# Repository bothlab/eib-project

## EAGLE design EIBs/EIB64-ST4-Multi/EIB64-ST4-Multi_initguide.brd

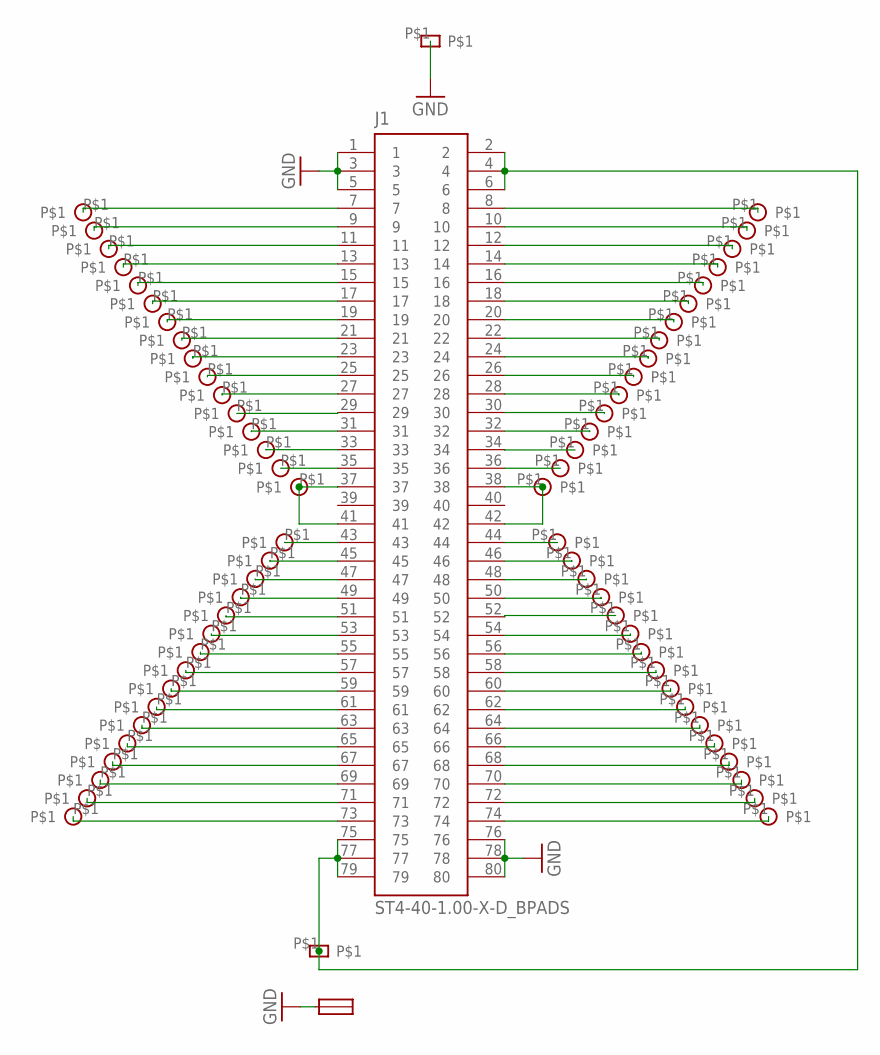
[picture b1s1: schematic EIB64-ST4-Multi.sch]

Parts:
J1: ST4-40-1.00-X-D_BPADS
U$1, U$3: EIB-GND-HOLE-PAD-SMALL
U$2: JMP-PAD-SMALL
U$5, U$6, U$7, U$8, U$9, U$10, U$11, U$12, U$13, U$14, U$15, U$16, U$17, U$18, U$19, U$20, U$21, U$22, U$23, U$24, U$25, U$26, U$27, U$28, U$29, U$30, U$31, U$32, U$33, U$34, U$35, U$36, U$37, U$38, U$39, U$40, U$41, U$42, U$43, U$44, U$45, U$46, U$47, U$48, U$49, U$50, U$51, U$52, U$53, U$54, U$55, U$56, U$57, U$58, U$59, U$60, U$61, U$62, U$63, U$64, U$65, U$66, U$67, U$68: EIB-TETRODE-HOLE-RS-PAD

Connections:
unnamed: J1.35, U$7.P$1
unnamed: J1.36, U$5.P$1
unnamed: J1.34, U$9.P$1
unnamed: J1.20, U$16.P$1
unnamed: J1.22, U$15.P$1
unnamed: J1.24, U$14.P$1
unnamed: J1.26, U$13.P$1
unnamed: J1.28, U$12.P$1
unnamed: J1.2, J1.4, J1.6, J1.75, J1.77, J1.79, U$3.P$1
unnamed: J1.1, J1.3, J1.5, J1.76, J1.78, J1.80, U$1.P$1, U$2.P$1
unnamed: J1.30, U$11.P$1
unnamed: J1.37, J1.41, U$8.P$1
unnamed: J1.32, U$10.P$1
unnamed: J1.74, U$52.P$1
unnamed: J1.18, U$17.P$1
unnamed: J1.16, U$18.P$1
unnamed: J1.14, U$19.P$1
unnamed: J1.12, U$20.P$1
unnamed: J1.10, U$21.P$1
unnamed: J1.8, U$22.P$1
unnamed: J1.33, U$23.P$1
unnamed: J1.31, U$24.P$1
unnamed: J1.29, U$25.P$1
unnamed: J1.27, U$26.P$1
unnamed: J1.25, U$27.P$1
unnamed: J1.23, U$28.P$1
unnamed: J1.21, U$29.P$1
unnamed: J1.19, U$30.P$1
unnamed: J1.17, U$31.P$1
unnamed: J1.15, U$32.P$1
unnamed: J1.13, U$33.P$1
unnamed: J1.11, U$34.P$1
unnamed: J1.9, U$35.P$1
unnamed: J1.7, U$36.P$1
unnamed: J1.72, U$51.P$1
unnamed: J1.70, U$50.P$1
unnamed: J1.68, U$49.P$1
unnamed: J1.66, U$48.P$1
unnamed: J1.64, U$47.P$1
unnamed: J1.62, U$46.P$1
unnamed: J1.60, U$45.P$1
unnamed: J1.58, U$44.P$1
unnamed: J1.56, U$43.P$1
unnamed: J1.54, U$42.P$1
unnamed: J1.52, U$41.P$1
unnamed: J1.50, U$40.P$1
unnamed: J1.48, U$39.P$1
unnamed: J1.46, U$38.P$1
unnamed: J1.44, U$37.P$1
unnamed: J1.38, J1.42, U$6.P$1
unnamed: J1.43, U$53.P$1
unnamed: J1.45, U$54.P$1
unnamed: J1.47, U$55.P$1
unnamed: J1.49, U$56.P$1
unnamed: J1.51, U$57.P$1
unnamed: J1.53, U$58.P$1
unnamed: J1.55, U$59.P$1
unnamed: J1.57, U$60.P$1
unnamed: J1.59, U$61.P$1
unnamed: J1.61, U$62.P$1
unnamed: J1.63, U$63.P$1
unnamed: J1.65, U$64.P$1
unnamed: J1.67, U$65.P$1
unnamed: J1.69, U$66.P$1
unnamed: J1.71, U$67.P$1
unnamed: J1.73, U$68.P$1

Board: 2 copper layers, 67 parts (0 on the bottom side), 66 nets, no tracks yet.
